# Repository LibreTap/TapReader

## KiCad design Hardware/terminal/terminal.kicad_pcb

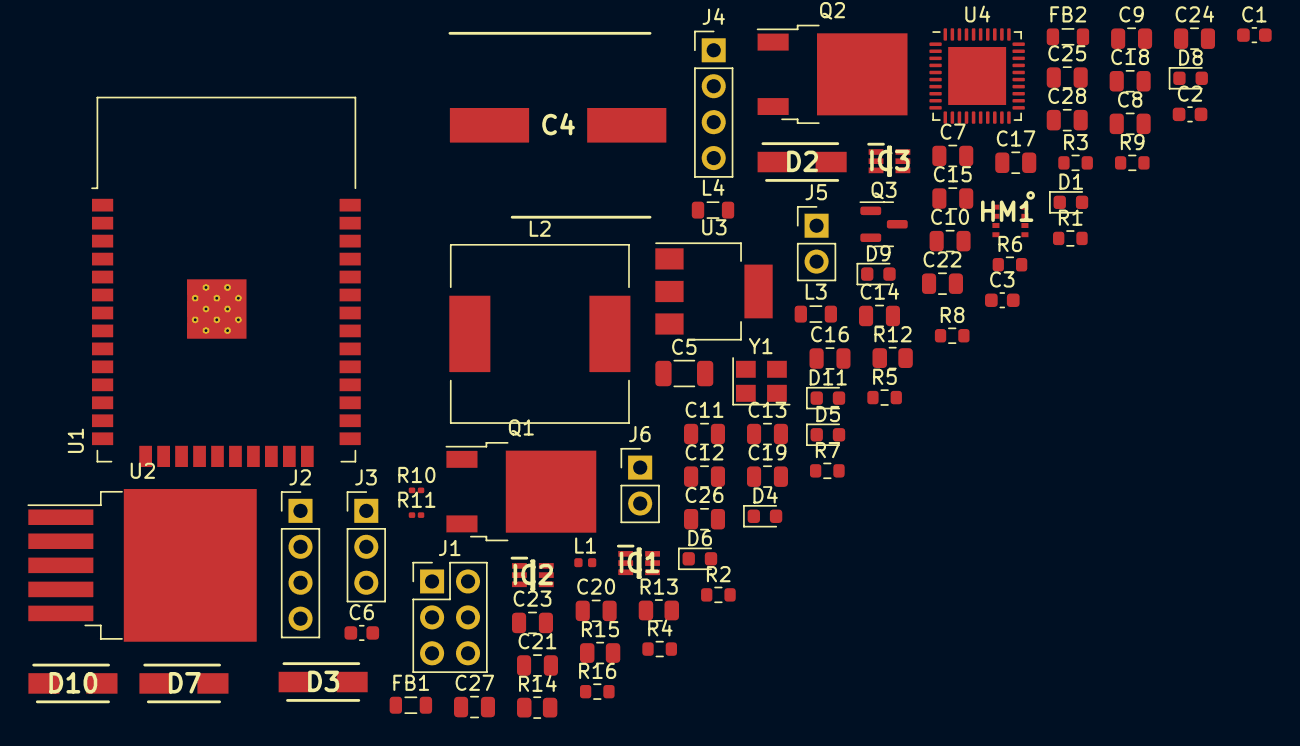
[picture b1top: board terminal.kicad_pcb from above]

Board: 2 copper layers, 79 parts (0 on the bottom side), 54 nets.

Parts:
C1, C2, C3, C6: 100nF @ 50V; C_0603_1608Metric
C4: 680uF; CAPAE1300X1400N
C5: 220 uF; C_1206_3216Metric
C7, C8, C13, C16: NC; C_0805_2012Metric
C9, C10: 100pF; C_0805_2012Metric
C11, C12: 22pF; C_0805_2012Metric
C14, C15: 220pF; C_0805_2012Metric
C17: 1000pF; C_0805_2012Metric
C18, C20, C23, C25, C28: 0.1uF; C_0805_2012Metric
C19, C21, C22, C24: 10uF; C_0805_2012Metric
C26, C27: 20pF; C_0805_2012Metric
D1: Signal; LED_0603_1608Metric
D2, D3, D7, D10: SS54; DIOM5026X262N
D4: PUMP; LED_0603_1608Metric
D5: AUX; LED_0603_1608Metric
D6: PWR 12; LED_0603_1608Metric
D8: PWR 5; LED_0603_1608Metric
D9: PWR 3.3; LED_0603_1608Metric
D11: Busy; LED_0603_1608Metric
FB1, FB2: FerriteBead; L_0805_2012Metric
HM1: BME280
IC1, IC2, IC3: SMF05CT1G; SOT65P210X110-6N
J1: Flash/Debug; PinHeader_2x03_P2.54mm_Vertical
J2: DIO; PinHeader_1x04_P2.54mm_Vertical
J3: PWR_IGN; PinHeader_1x03_P2.54mm_Vertical
J4: I2C; PinHeader_1x04_P2.54mm_Vertical
J5: PUMP; PinHeader_1x02_P2.54mm_Vertical
J6: AUX; PinHeader_1x02_P2.54mm_Vertical
L1: 5.6 nH; L_0402_1005Metric
L2: 33uH; L_12x12mm_H8mm
L3, L4: 560nH; L_0805_2012Metric
Q1, Q2: NCE6050KA; TO-252-2
Q3: BSS138; SOT-23
R1, R2, R3: 10k; R_0603_1608Metric
R4, R9, R16: 150R; R_0603_1608Metric
R5, R6, R7: 1k2; R_0603_1608Metric
R8: 330R; R_0603_1608Metric
R10, R11: NC; R_0201_0603Metric
R12, R13: 1.5; R_0805_2012Metric
R14: 1k69; R_0805_2012Metric
R15: 1k; R_0805_2012Metric
U1: ESP32-WROOM-32D; ESP32-WROOM-32
U2: LM2596S-5; TO-263-5_TabPin3
U3: AMS1117-3.3; SOT-223-3_TabPin2
U4: PN5321A3HN_C1xx; HVQFN-40-1EP_6x6mm_P0.5mm_EP4.1x4.1mm
Y1: 27.12 MHz; Crystal_SMD_3225-4Pin_3.2x2.5mm

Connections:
+3.3V: C3.2, C6.1, HM1.6 (VDDIO), HM1.8 (VDD), IC1.6 (K_5), J2.2, J4.2, L1.1, R9.1, U3.2 (VO)
+5V: C5.1, IC3.1 (K_1), J1.2, L2.2, R8.1, U2.4 (FB), U3.3 (VI)
+12V: C4.1, D7.1, J5.2, J6.2, R5.1, R6.1, R7.1, U2.1 (VIN)
AUX_CTRL: IC1.4 (K_3), Q2.1 (G), R3.1, U1.13 (IO14)
AUX_IN: IC1.1 (K_1), J2.4, U1.9 (IO33)
CLK: HM1.4 (SCK), U1.30 (IO18)
CON_12V: D7.2, J3.3
CON_MOTOR: D2.1, D4.1 (K), J5.1, Q1.2 (D)
CON_SW_AUX: D3.1, D5.1 (K), J6.1, Q2.2 (D)
CS: HM1.2 (CSB), U1.11 (IO26)
EN: C1.1, IC3.4 (K_3), J1.6, R1.2, U1.3 (EN)
GND: C1.2, C2.1, C3.1, C4.2, C5.2, C6.2, C7.2, C8.1, C9.2, C10.1, C14.2, C15.1, C18.2, C19.1, C20.1, C21.1, C22.1, C23.2, C24.2, C25.2, C26.1, C27.2, C28.1, D1.1 (K), D2.2, D3.2, D6.1 (K), D8.1 (K), D9.1 (K), D10.2, HM1.1 (GND_1), HM1.7 (GND_2), IC1.2 (A), IC2.2 (A), IC3.2 (A), J1.1, J2.1, J4.1, Q1.3 (S), Q2.3 (S), Q3.2 (S), R2.2, R3.2, R10.2, R11.1, U1.1 (GND), U1.15 (GND), U1.38 (GND), U1.39 (GND), U2.3 (GND), U2.5 (~ON/OFF), U3.1 (GND), U4.1 (DVSS), U4.3 (TVSS1), U4.7 (TVSS2), U4.11 (AVSS), U4.16 (I0), U4.18 (TESTEN), U4.41 (AVSS)
IO0: IC3.3 (K_2), J1.5, U1.25 (IO0)
IO4: IC2.3 (K_2), U1.26 (IO4)
IO16: IC2.4 (K_3), U1.27 (IO16)
IO25: IC2.1 (K_1), U1.10 (IO25)
MISO: HM1.5 (SDO), U1.31 (IO19), U4.29 (MISO/P71)
MOSI: HM1.3 (SDI), U1.37 (IO23), U4.28 (MOSI/SDA/HSU_TX)
MOTO_CTRL: IC1.5 (K_4), Q1.1 (G), R2.1, U1.16 (IO13)
unnamed: C8.2, C10.2, C12.2, C16.2, R13.2
unnamed: C7.1, C9.1, C11.1, C13.1, R12.1
unnamed: C11.2, C13.2, C14.1, L3.1
unnamed: C12.1, C15.2, C16.1, L4.1, R14.1
unnamed: C17.1, R14.2
unnamed: C17.2, R15.1, U4.10 (RX)
unnamed: C18.1, R15.2, U4.9 (VMID)
unnamed: C19.2, U4.37 (SVDD)
unnamed: C21.2, FB1.2, U4.5 (TVDD)
unnamed: C23.1, C24.1, FB2.2, U4.8 (AVDD)
unnamed: C26.2, U4.14 (OSCIN), Y1.2
unnamed: C27.1, U4.15 (OSCOUT), Y1.1
unnamed: D1.2 (A), R4.2
unnamed: D4.2 (A), R5.2
unnamed: D5.2 (A), R6.2
unnamed: D6.2 (A), R7.2
unnamed: D8.2 (A), R8.2
unnamed: D9.2 (A), R9.2
unnamed: D10.1, L2.1, U2.2 (OUT)
unnamed: D11.1 (K), Q3.3 (D)
unnamed: D11.2 (A), R16.2
unnamed: L3.2, U4.4 (TX1)
unnamed: L4.2, U4.6 (TX2)
unnamed: Q3.1 (G), U4.25 (P70_IRQ)
unnamed: R4.1, U1.12 (IO27)
unnamed: R10.1, R12.2
unnamed: R11.2, R13.1
RX: IC3.5 (K_4), J1.3, U1.34 (RXD0/IO3)
SCL: IC2.5 (K_4), J4.4, U1.36 (IO22), U4.30 (SCK/P72)
SDA: IC2.6 (K_5), J4.3, U1.33 (IO21)
TX: IC3.6 (K_5), J1.4, U1.35 (TXD0/IO1)
VCC: C20.2, C22.2, FB1.1, FB2.1, U4.39 (DVDD)
VDD: C25.1, C28.2, R16.1, U4.17 (I1), U4.23 (PVDD), U4.40 (VBAT)
VDDESP: C2.2, L1.2, R1.1, U1.2 (VDD)
WET: IC1.3 (K_2), J2.3, U1.8 (IO32)

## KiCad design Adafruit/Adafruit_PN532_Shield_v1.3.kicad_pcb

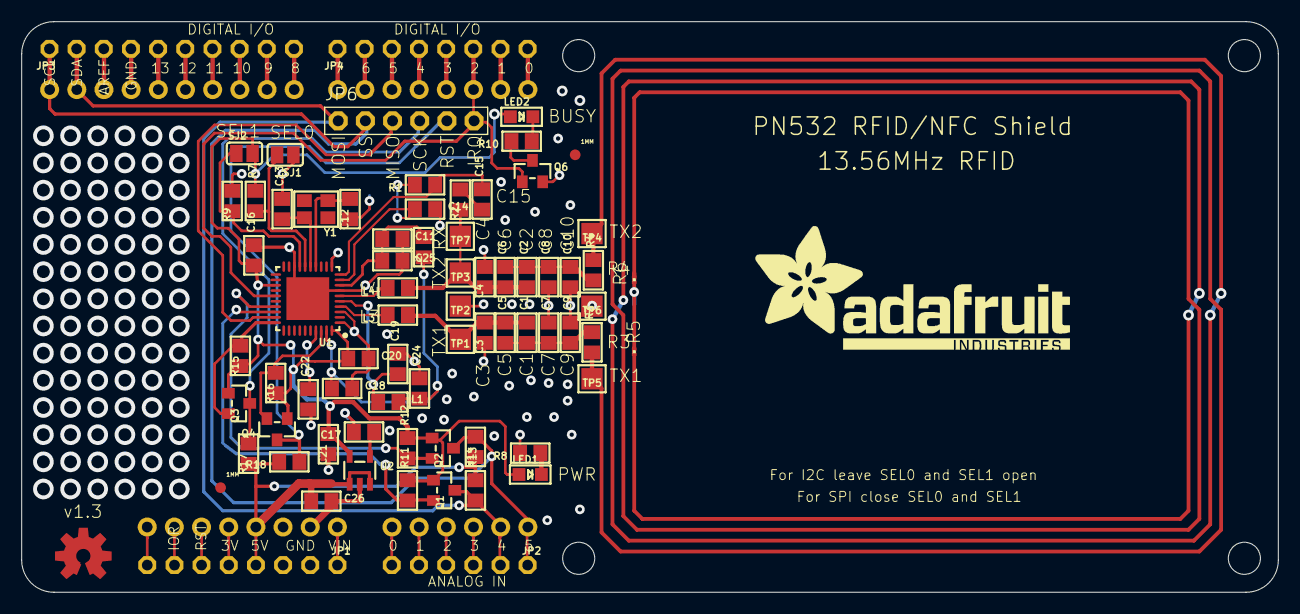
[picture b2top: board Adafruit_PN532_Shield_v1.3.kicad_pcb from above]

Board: 2 copper layers, 117.5 x 53.3 mm, 80 parts (0 on the bottom side), 59 nets.

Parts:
@HOLE0, @HOLE1, @HOLE2, @HOLE3: (no value)
C1, C2: 22pF; 0805
C3, C4: 220pF; 0805
C5, C6, C9, C10: NC; 0805
C7, C8: 100pF; 0805
C11, C14, C16, C17, C20, C24: 0.1µF; 0805
C12, C13: 33pF; 0805
C15: 1000pF; 0805
C18, C19, C21, C22, C25, C26: 10µF; 0805
FID1, FID2: FIDUCIAL1X2.5; FIDUCIAL-1X2.5
JP1, JP4: 1X08_ROUND_70
JP2: 1X06_ROUND_70
JP3: 1X10_ROUND70
JP6: 1X06-BIG
L1, L2: FERRITE; 0805
L3, L4: 560nH; 0805
LED1: PWR; CHIPLED_0805
LED2: IRQ; CHIPLED_0805
Q1, Q2, Q3, Q4, Q6: BSS138; SOT23-WIDE
R1: 1.0K; 0805
R2: 1.69K; 0805
R3, R4: 1.5; 0805
R5, R6: NC; R0201
R7, R9, R11, R12, R13, R14, R15, R16, R17, R18: 10K; 0805
R8, R10: TBD; 0805
SJ1, SJ2: SOLDERJUMPER_REFLOW_NOPASTE
TP1: TX1_POST; TESTPOINT_PAD_2MM
TP2, TP6: TGND; TESTPOINT_PAD_2MM
TP3: TX2_POST; TESTPOINT_PAD_2MM
TP4: TX2_PRE; TESTPOINT_PAD_2MM
TP5: TX1_PRE; TESTPOINT_PAD_2MM
TP7: RX; TESTPOINT_PAD_2MM
U1: PN532; HVQFN40-6X6
U2: ADP122(3.3V); SOT23-5
U3: ARDUINOR3NODIM; ARDUINOR3-NODIM
U$3: ADAFRUIT_TEXT_30MM
U$50: OSHWLOGO_TOP_0.2
Y1: 27.12MHz; CRYSTAL_3.2X2.5

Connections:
5.0V: C26.1, JP1.4, R13.2, R14.2, R17.2, R18.2, U2.1, U2.3, U3.5V
GND: C3.2, C4.1, C7.2, C8.1, C9.2, C10.1, C11.2, C12.2, C13.2, C14.2, C16.2, C17.2, C18.2, C19.2, C20.2, C21.2, C22.1, C24.2, C25.2, C26.2, JP1.2, JP1.3, JP3.4, Q6.2, R5.2, R6.1, R8.2, R9.1, SJ1.1, TP2.P$1, TP6.P$1, U1.1, U1.3, U1.7, U1.11, U1.18, U1.TP, U2.2, U3.GND, U3.GND1, U3.GND2
IRQ: JP4.6, JP6.6, Q6.1, U1.25, U3.D2
MISO: JP6.3, U1.29
MOSI/SDA/TX: Q1.2, R11.1, U1.28
MOSI/SDA_5.0V: JP2.2, JP3.2, JP6.1, Q1.3, R13.1, U3.A4, U3.SDA
unnamed: L3.2, U1.4
unnamed: L4.2, U1.6
unnamed: C1.2, C3.1, C5.2, L3.1, TP1.P$1
unnamed: R3.1, R6.2, TP5.P$1
unnamed: R4.2, R5.1, TP4.P$1
unnamed: LED1.C, R8.1
unnamed: C12.1, U1.14, Y1.1
unnamed: C13.1, U1.15, Y1.2
unnamed: C15.1, R2.1
unnamed: C14.1, R1.2, U1.9
unnamed: C15.2, R1.1, U1.10
unnamed: C2.1, C4.2, C6.1, L4.1, R2.2, TP3.P$1, TP7.P$1
unnamed: C11.1, C25.1, L2.1, U1.8
unnamed: C19.1, L1.1, U1.5
unnamed: JP1.1, U3.VIN
unnamed: JP1.5, U3.3V
unnamed: JP1.6, U3.RESET
unnamed: JP1.7, U3.IOREF
unnamed: JP1.8, U3.RESERVED
unnamed: JP2.3, U3.A3
unnamed: JP2.4, U3.A2
unnamed: JP2.5, U3.A1
unnamed: JP2.6, U3.A0
unnamed: JP3.3, U3.AREF
unnamed: JP3.5, U3.D13
unnamed: JP3.6, U3.D12
unnamed: JP3.7, U3.D11
unnamed: JP3.8, U3.D10
unnamed: JP3.9, U3.D9
unnamed: JP3.10, U3.D8
unnamed: JP4.1, U3.D7
unnamed: JP4.2, U3.D6
unnamed: JP4.3, U3.D5
unnamed: JP4.4, U3.D4
unnamed: JP4.5, U3.D3
unnamed: LED2.C, R10.1
unnamed: JP4.7, U3.D1
unnamed: JP4.8, U3.D0
unnamed: Q6.3, R10.2
unnamed: C17.1, U2.4
unnamed: C22.2, U1.37
NSS/SCL/RX: Q2.2, R12.1, U1.27
NSS/SCL_5.0V: JP2.1, JP3.1, JP6.2, Q2.3, R14.1, U3.A5, U3.SCL
RSTPD_N: Q4.2, R16.1, U1.38
RSTPD_N_5.0V: JP6.5, Q4.3, R18.1
SCK: Q3.2, R15.1, U1.30
SCK_5.0V: JP6.4, Q3.3, R17.1
SEL0: R7.1, SJ1.2, U1.16
SEL1: R9.2, SJ2.1, U1.17
TX1_ANTENNA: C1.1, C5.1, C7.1, C9.1, R3.2
TX2_ANTENNA: C2.2, C6.2, C8.2, C10.2, R4.1
VCC: C18.1, C24.1, L1.2, L2.2, U1.39
VDD: C16.1, C20.1, C21.1, LED1.A, LED2.A, Q1.1, Q2.1, Q3.1, Q4.1, R7.2, R11.2, R12.2, R15.2, R16.2, SJ2.2, U1.23, U1.40, U2.5

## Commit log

2025-11-13 Add initial prototype version
2025-11-13 cleanup: remove unnessary libs and create RFID-Secure-Doorlock lib
2025-11-13 feat: implement MQTT serialization and deserialization functions
    - Added mqtt_serialization.cpp and mqtt_types.cpp to handle message envelope serialization, deserialization, and type conversions.
    - Implemented functions for generating timestamps and UUIDs.
    - Created payload serialization functions for various events including status change, mode change, and error handling.
    - Developed validation functions for tag UIDs, hex keys, UUIDs, and device IDs.
    - Introduced unit tests for serialization and deserialization processes, including round-trip tests and validation checks.
    - Added mock implementations for Arduino functions to facilitate unit testing in a native environment.
2025-11-13 cleanup: remove schemas
2025-11-13 refactor: introduce `#pragma once` as guard, move `run_config_portal` into config.cpp and make main a cpp file
2025-12-04 feat: add mTLS certificate generation script for secure MQTT connections
